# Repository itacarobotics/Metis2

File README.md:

# Metis2
Metis2 is the latest enhanced version of Metis. This project is currently under development, however below is an overview of the changes.

## Mechanics
The new delta robot provides a modular design, with less components and assembly time. An extra degree of freedom has been added to the end effector to rotate around the z-axis. Furthermore, the size of the new robot is significantly smaller than the previous one, therefore it can better fits in smaller environments, such as a small production line.

## Electronics
The control unit of the robot is the BIGTREETECH-SKR-mini-E3 board, which is a main board for 3D printers. Beyond that, a custom PCB has been designed as a shield for the main board, in order to better manage GPIOs and power supply for encoders and motors using terminal blocks.

## Firmware
The control software of the robot is subdivided in two parts based on abstraction levels. The low-level firmware runs on an STM32-G01B1RCT6 micro-controller integrated onto the motherboard. The firmware runs different state machines, each responisble for the comunication, processing data for the trajectory generation and inverse geometry and controlling the closed loop stepper motors. The higher level software controls the position of the robot using the GCODE format.

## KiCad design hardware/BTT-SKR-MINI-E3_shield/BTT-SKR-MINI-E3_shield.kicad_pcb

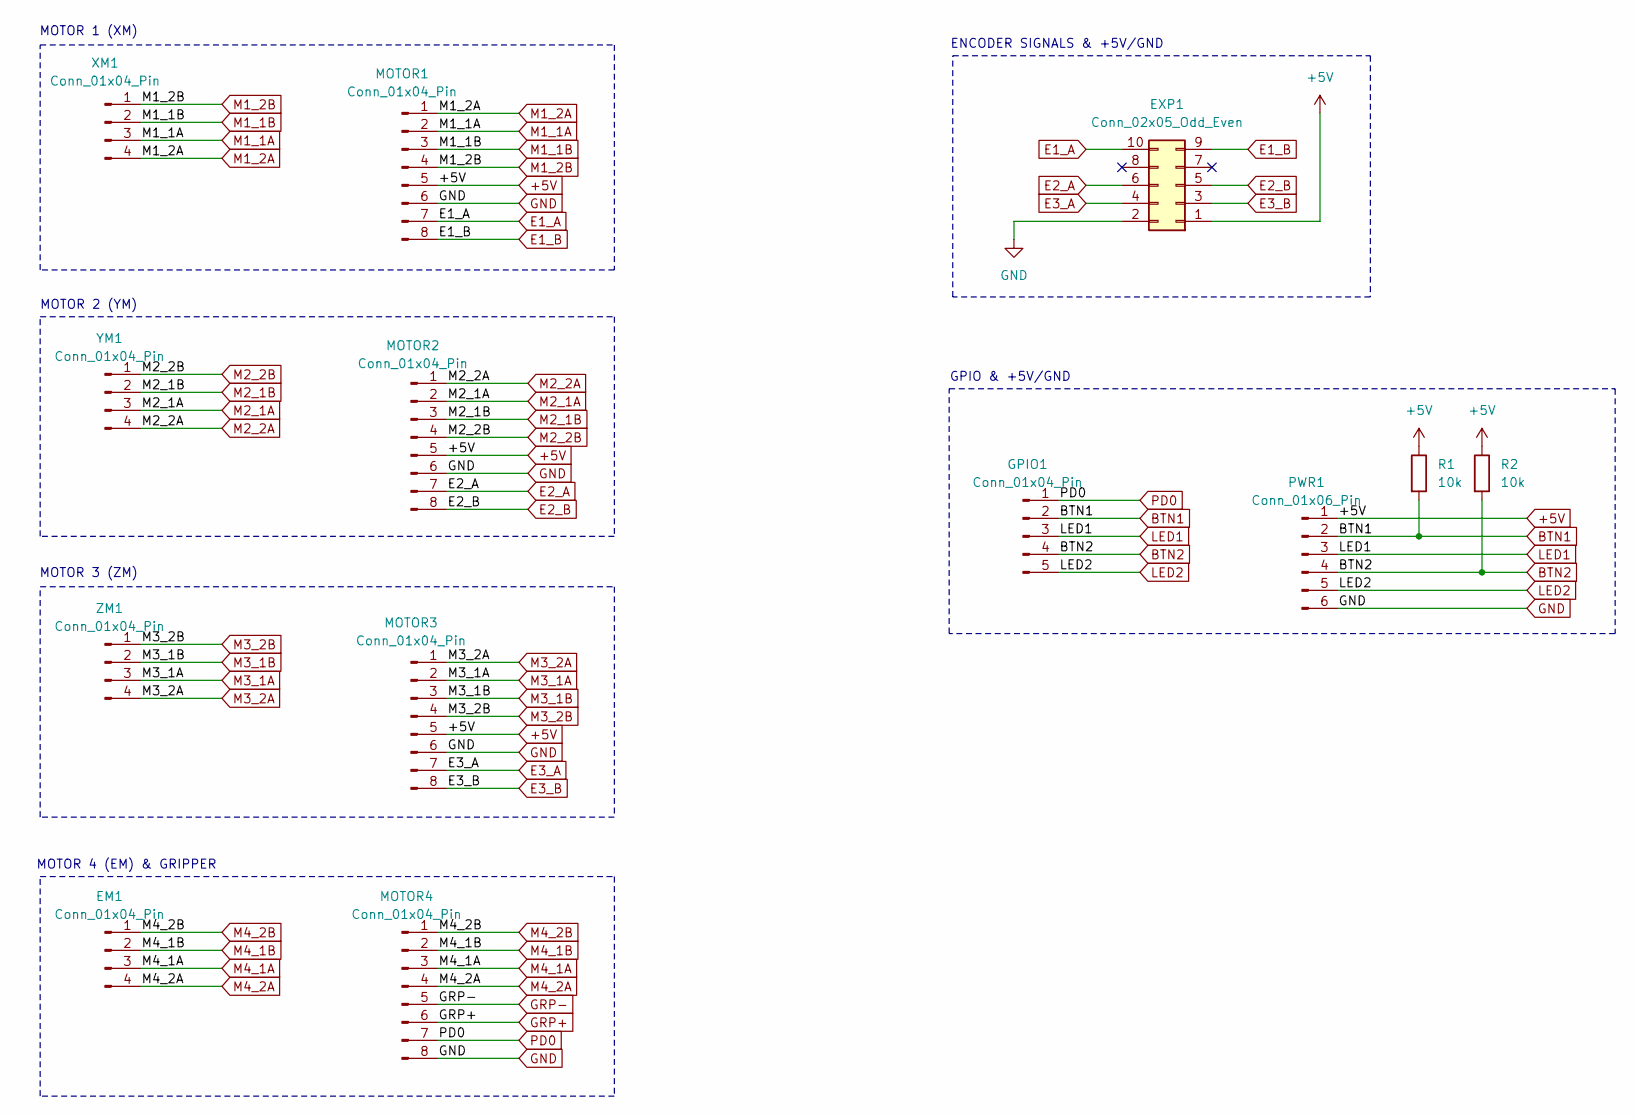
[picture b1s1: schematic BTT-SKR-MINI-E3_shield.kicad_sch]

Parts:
EM1: Conn_01x04_Pin; JST_XH_B4B-XH-A_1x04_P2.50mm_Vertical
EXP1: Conn_02x05_Odd_Even; IDC-Header_2x05_P2.54mm_Vertical
GPIO1: Conn_01x04_Pin; PinHeader_1x05_P2.54mm_Vertical
MOTOR1, MOTOR2, MOTOR3, MOTOR4: Conn_01x04_Pin; MC1.5_8-G-3.5
PWR1: Conn_01x06_Pin; MV1.5_6-G-3.5
R1, R2: 10k; R_0805_2012Metric
XM1: Conn_01x04_Pin; JST_XH_B4B-XH-A_1x04_P2.50mm_Vertical
YM1: Conn_01x04_Pin; JST_XH_B4B-XH-A_1x04_P2.50mm_Vertical
ZM1: Conn_01x04_Pin; JST_XH_B4B-XH-A_1x04_P2.50mm_Vertical

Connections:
+5V: EXP1.1, MOTOR1.5, MOTOR2.5, MOTOR3.5, PWR1.1, R1.1, R2.1
BTN1: GPIO1.2, PWR1.2, R1.2
BTN2: GPIO1.4, PWR1.4, R2.2
E1_A: EXP1.10, MOTOR1.7
E1_B: EXP1.9, MOTOR1.8
E2_A: EXP1.6, MOTOR2.7
E2_B: EXP1.5, MOTOR2.8
E3_A: EXP1.4, MOTOR3.7
E3_B: EXP1.3, MOTOR3.8
GND: EXP1.2, MOTOR1.6, MOTOR2.6, MOTOR3.6, MOTOR4.8, PWR1.6
GRP+: MOTOR4.6; also elsewhere on the board
GRP-: MOTOR4.5; also elsewhere on the board
LED1: GPIO1.3, PWR1.3
LED2: GPIO1.5, PWR1.5
M1_1A: MOTOR1.2, XM1.3
M1_1B: MOTOR1.3, XM1.2
M1_2A: MOTOR1.1, XM1.4
M1_2B: MOTOR1.4, XM1.1
M2_1A: MOTOR2.2, YM1.3
M2_1B: MOTOR2.3, YM1.2
M2_2A: MOTOR2.1, YM1.4
M2_2B: MOTOR2.4, YM1.1
M3_1A: MOTOR3.2, ZM1.3
M3_1B: MOTOR3.3, ZM1.2
M3_2A: MOTOR3.1, ZM1.4
M3_2B: MOTOR3.4, ZM1.1
M4_1A: EM1.3, MOTOR4.3
M4_1B: EM1.2, MOTOR4.2
M4_2A: EM1.4, MOTOR4.4
M4_2B: EM1.1, MOTOR4.1
PD0: GPIO1.1, MOTOR4.7

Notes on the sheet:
ENCODER SIGNALS & +5V/GND
MOTOR 3 (ZM)
MOTOR 4 (EM) & GRIPPER
MOTOR 1 (XM)
GPIO & +5V/GND
MOTOR 2 (YM)

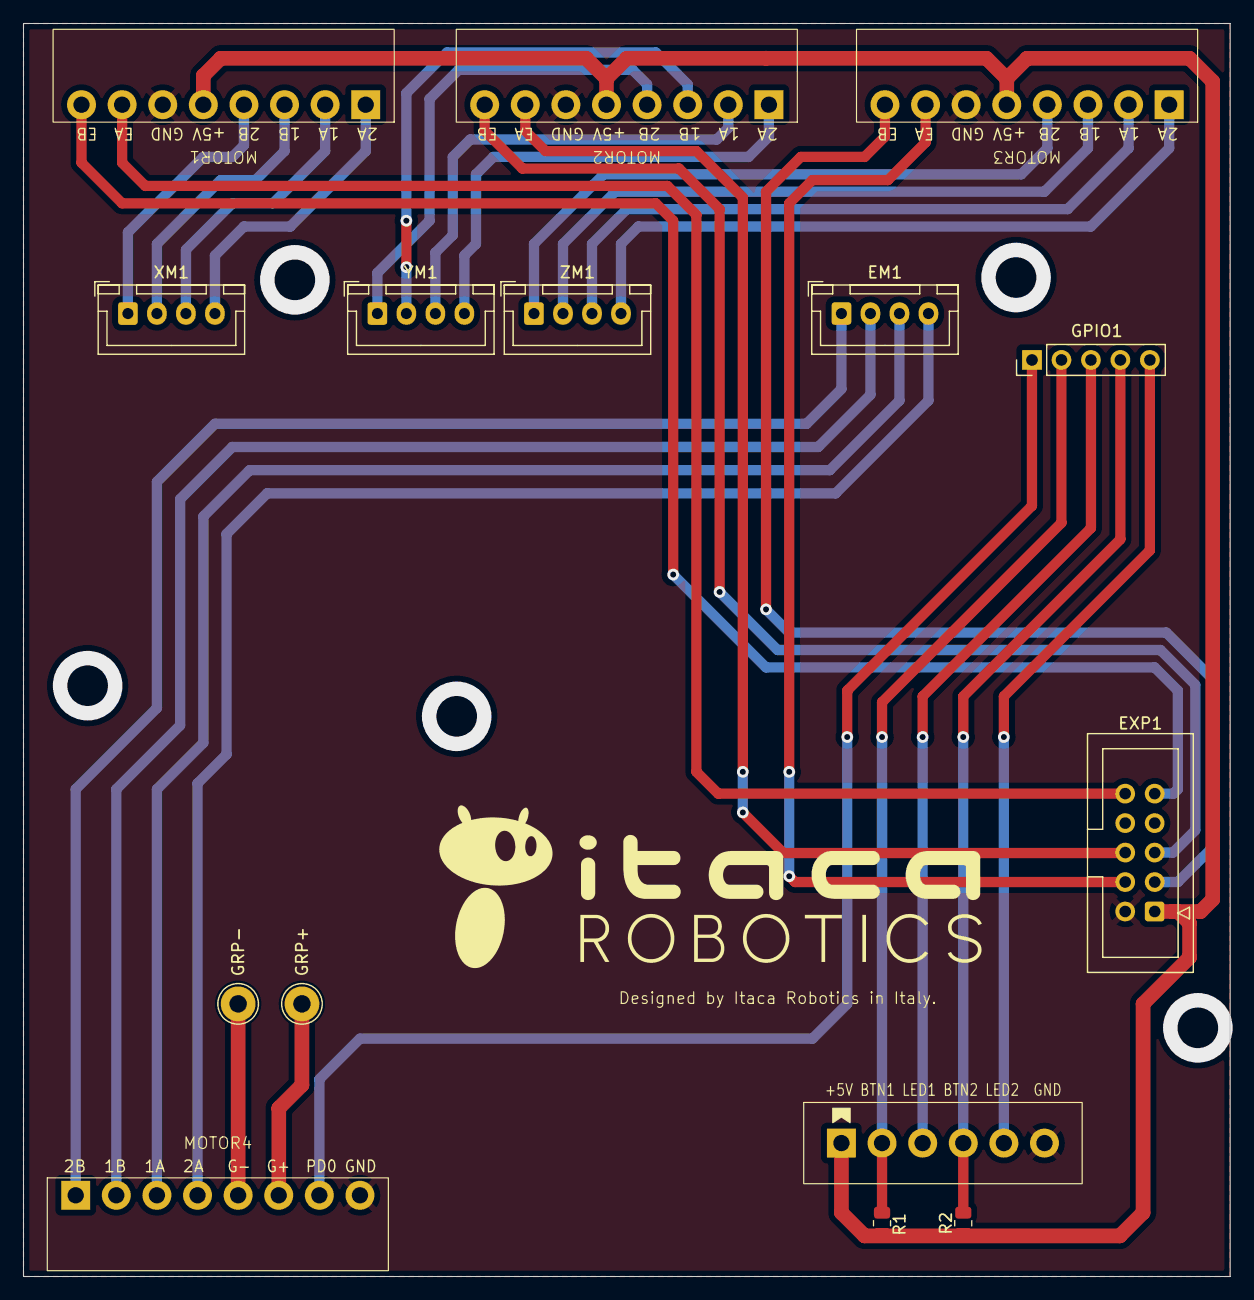
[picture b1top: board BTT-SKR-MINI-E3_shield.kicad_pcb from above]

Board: 2 copper layers, 104.0 x 108.0 mm, 15 parts (0 on the bottom side), 31 nets.

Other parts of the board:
GRP+: TestPoint_THTPad_D3.0mm_Drill1.5mm
GRP-: TestPoint_THTPad_D3.0mm_Drill1.5mm

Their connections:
GRP+: GRP+.1; also elsewhere on the board
GRP-: GRP-.1; also elsewhere on the board

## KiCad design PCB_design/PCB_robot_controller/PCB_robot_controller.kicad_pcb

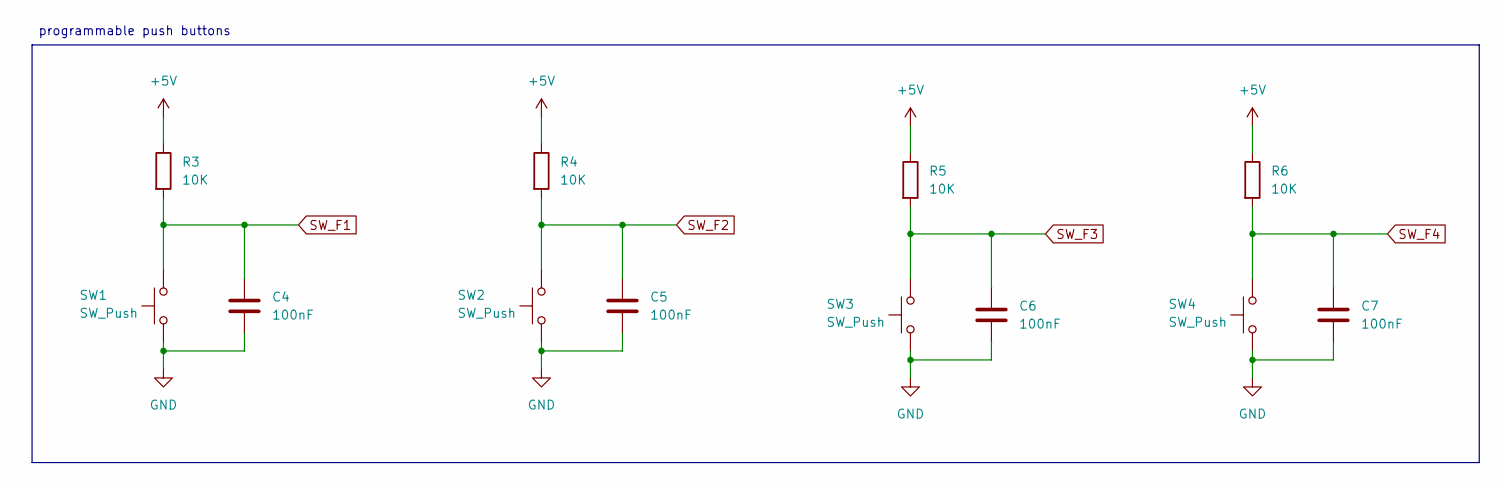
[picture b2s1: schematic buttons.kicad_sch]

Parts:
C4, C5, C6, C7: 100nF; C_0805_2012Metric
R3, R4, R5, R6: 10K; R_0805_2012Metric
SW1, SW2, SW3, SW4: SW_Push; SW_PUSH_6mm_H5mm

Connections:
GND: C4.2, C5.2, C6.2, C7.2, SW1.1, SW2.1, SW3.1, SW4.1; also elsewhere on the board
SW_F1: C4.1, R3.2, SW1.2; also elsewhere on the board
SW_F2: C5.1, R4.2, SW2.2; also elsewhere on the board
SW_F3: C6.1, R5.2, SW3.2; also elsewhere on the board
SW_F4: C7.1, R6.2, SW4.2; also elsewhere on the board

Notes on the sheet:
programmable push buttons

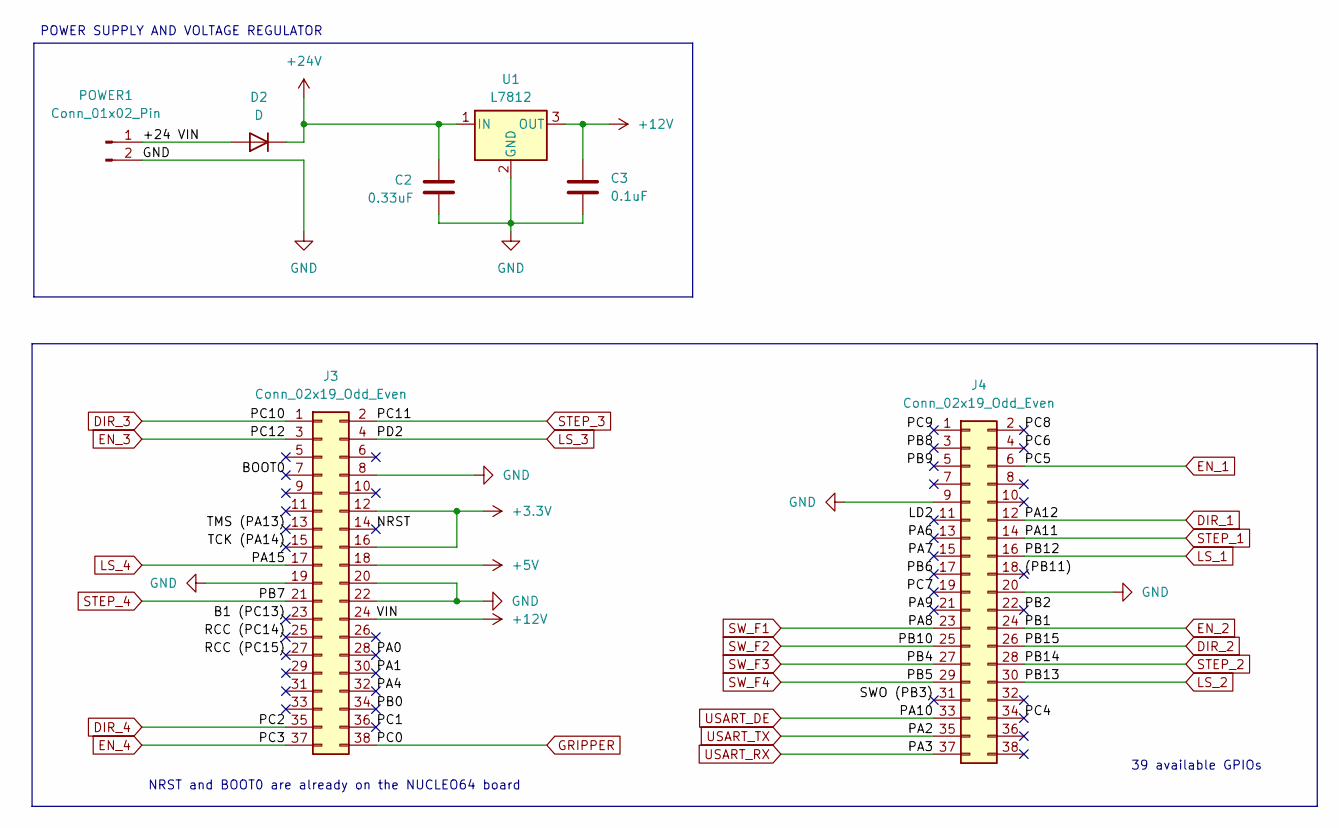
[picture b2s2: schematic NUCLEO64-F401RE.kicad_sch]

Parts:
C2: 0.33uF; C_0805_2012Metric
C3: 0.1uF; C_0805_2012Metric
D2: D; D_0805_2012Metric
J3, J4: Conn_02x19_Odd_Even; PinSocket_2x19_P2.54mm_Vertical
POWER1: Conn_01x02_Pin; TerminalBlock 45 degrees, pitch 3.5mm, 2 pins, WAGO 250-102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
U1: L7812; TO-220-3_Horizontal_TabDown

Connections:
+3.3V: J3.12, J3.16
+12V: C3.1, J3.24, U1.3 (OUT)
+24V: C2.1, D2.1 (K), U1.1 (IN); also elsewhere on the board
/NUCLEO64-F401RE/(PB11): J4.18
/NUCLEO64-F401RE/+24 VIN: D2.2 (A), POWER1.1; also elsewhere on the board
/NUCLEO64-F401RE/B1 (PC13): J3.23
/NUCLEO64-F401RE/BOOT0: J3.7
/NUCLEO64-F401RE/LD2: J4.11
/NUCLEO64-F401RE/NRST: J3.14
/NUCLEO64-F401RE/PA0: J3.28
/NUCLEO64-F401RE/PA1: J3.30
/NUCLEO64-F401RE/PA4: J3.32
/NUCLEO64-F401RE/PA6: J4.13
/NUCLEO64-F401RE/PA7: J4.15
/NUCLEO64-F401RE/PA9: J4.21
/NUCLEO64-F401RE/PB0: J3.34
/NUCLEO64-F401RE/PB2: J4.22
/NUCLEO64-F401RE/PB6: J4.17
/NUCLEO64-F401RE/PB8: J4.3
/NUCLEO64-F401RE/PB9: J4.5
/NUCLEO64-F401RE/PC1: J3.36
/NUCLEO64-F401RE/PC4: J4.34
/NUCLEO64-F401RE/PC6: J4.4
/NUCLEO64-F401RE/PC7: J4.19
/NUCLEO64-F401RE/PC8: J4.2
/NUCLEO64-F401RE/PC9: J4.1
/NUCLEO64-F401RE/RCC (PC14): J3.25
/NUCLEO64-F401RE/RCC (PC15): J3.27
/NUCLEO64-F401RE/SWO (PB3): J4.31
/NUCLEO64-F401RE/TCK (PA14): J3.15
/NUCLEO64-F401RE/TMS (PA13): J3.13
DIR_1: J4.12; also elsewhere on the board
DIR_2: J4.26; also elsewhere on the board
DIR_3: J3.1; also elsewhere on the board
DIR_4: J3.35; also elsewhere on the board
GND: C2.2, C3.2, J3.8, J3.19, J3.20, J3.22, J4.9, J4.20, POWER1.2, U1.2 (GND); also elsewhere on the board
GRIPPER: J3.38; also elsewhere on the board
LS_1: J4.16; also elsewhere on the board
LS_2: J4.30; also elsewhere on the board
LS_3: J3.4; also elsewhere on the board
LS_4: J3.17; also elsewhere on the board
STEP_1: J4.14; also elsewhere on the board
STEP_2: J4.28; also elsewhere on the board
STEP_3: J3.2; also elsewhere on the board
STEP_4: J3.21; also elsewhere on the board
SW_F1: J4.23; also elsewhere on the board
SW_F2: J4.25; also elsewhere on the board
SW_F3: J4.27; also elsewhere on the board
SW_F4: J4.29; also elsewhere on the board
USART_DE: J4.33; also elsewhere on the board
USART_RX: J4.37; also elsewhere on the board
USART_TX: J4.35; also elsewhere on the board

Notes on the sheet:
39 available GPIOs
POWER SUPPLY AND VOLTAGE REGULATOR
NRST and BOOT0 are already on the NUCLEO64 board

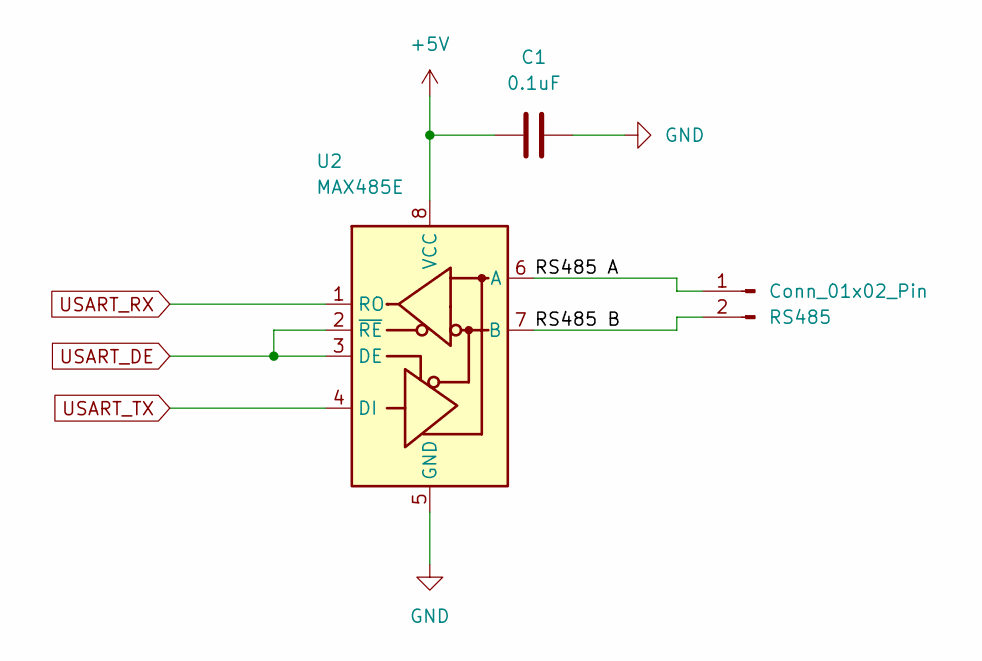
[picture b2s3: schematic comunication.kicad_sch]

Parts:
C1: 0.1uF; C_0805_2012Metric
RS485: Conn_01x02_Pin; TerminalBlock 45 degrees, pitch 3.5mm, 2 pins, WAGO 250-102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
U2: MAX485E; SO-8_3.9x4.9mm_P1.27mm

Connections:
/comunication/RS485 A: RS485.1, U2.6 (A); also elsewhere on the board
/comunication/RS485 B: RS485.2, U2.7 (B); also elsewhere on the board
GND: C1.2, U2.5 (GND); also elsewhere on the board
USART_DE: U2.2 (~RE), U2.3 (DE); also elsewhere on the board
USART_RX: U2.1 (RO); also elsewhere on the board
USART_TX: U2.4 (DI); also elsewhere on the board

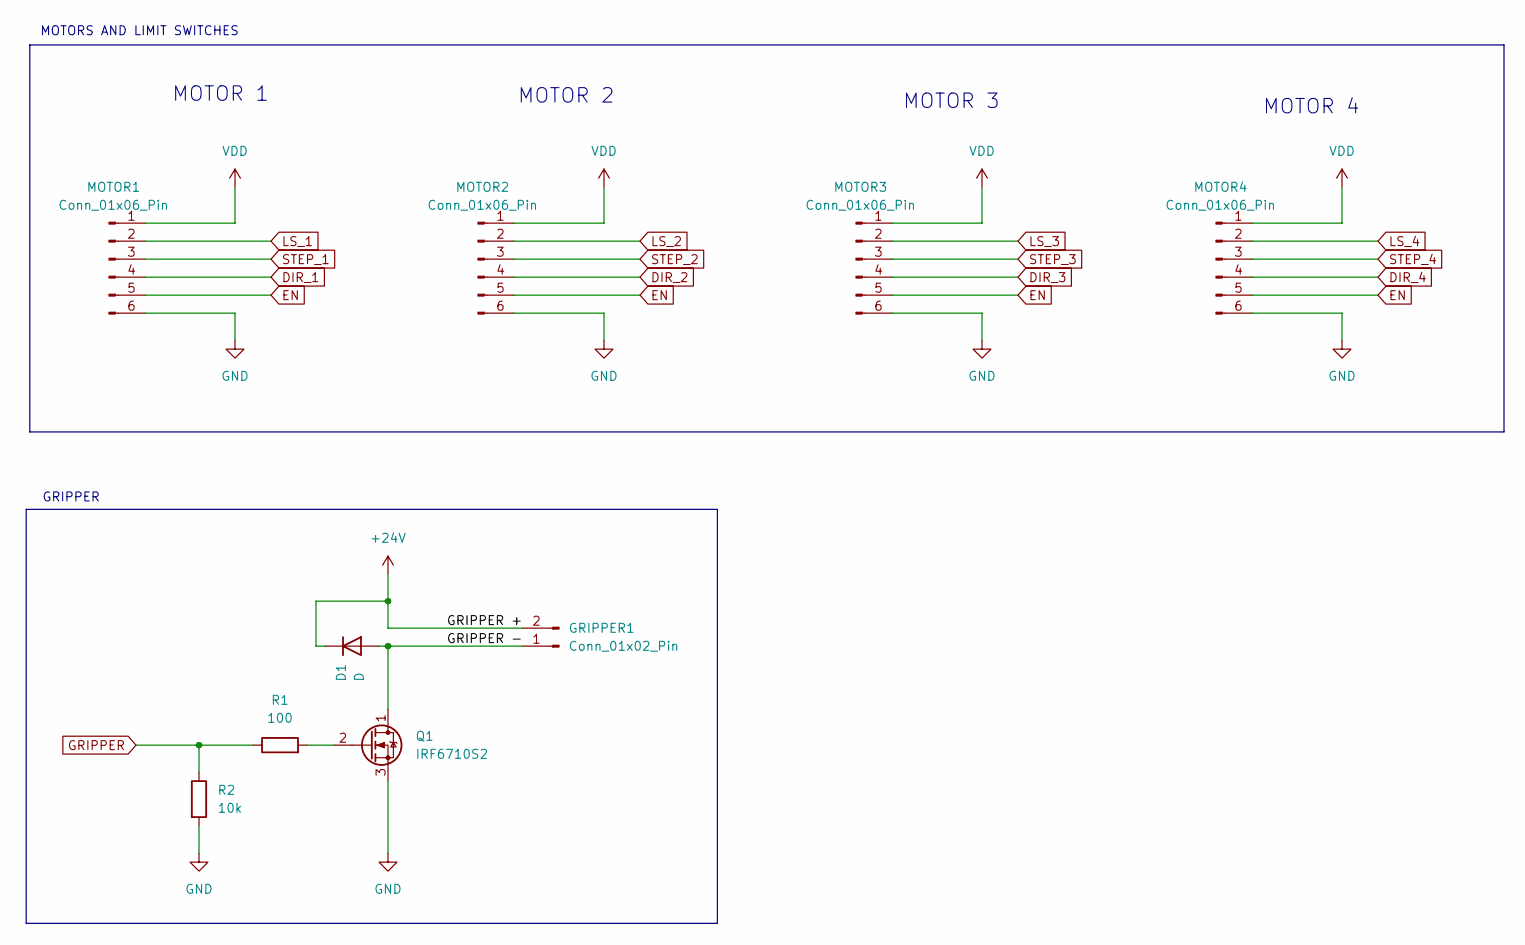
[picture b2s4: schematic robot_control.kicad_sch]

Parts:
D1: D; D_0805_2012Metric
GRIPPER1: Conn_01x02_Pin; TerminalBlock 45 degrees, pitch 3.5mm, 2 pins, WAGO 250-102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
MOTOR1, MOTOR2, MOTOR3, MOTOR4: Conn_01x06_Pin; TerminalBlock 45 degrees, pitch 3.5mm, 6 pins, WAGO 250-102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
Q1: IRF6710S2; TO-220-3_Vertical
R1: 100; R_0805_2012Metric
R2: 10k; R_0805_2012Metric

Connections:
+24V: D1.1 (K), GRIPPER1.2; also elsewhere on the board
/robot_control/GRIPPER -: D1.2 (A), GRIPPER1.1, Q1.1 (D); also elsewhere on the board
DIR_1: MOTOR1.4; also elsewhere on the board
DIR_2: MOTOR2.4; also elsewhere on the board
DIR_3: MOTOR3.4; also elsewhere on the board
DIR_4: MOTOR4.4; also elsewhere on the board
GND: MOTOR1.6, MOTOR2.6, MOTOR3.6, MOTOR4.6, Q1.3 (S), R2.2; also elsewhere on the board
GRIPPER: R1.1, R2.1; also elsewhere on the board
LS_1: MOTOR1.2; also elsewhere on the board
LS_2: MOTOR2.2; also elsewhere on the board
LS_3: MOTOR3.2; also elsewhere on the board
LS_4: MOTOR4.2; also elsewhere on the board
unnamed: Q1.2 (G), R1.2
STEP_1: MOTOR1.3; also elsewhere on the board
STEP_2: MOTOR2.3; also elsewhere on the board
STEP_3: MOTOR3.3; also elsewhere on the board
STEP_4: MOTOR4.3; also elsewhere on the board

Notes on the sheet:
MOTOR 2
MOTOR 4
MOTORS AND LIMIT SWITCHES
MOTOR 3
GRIPPER
MOTOR 1

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
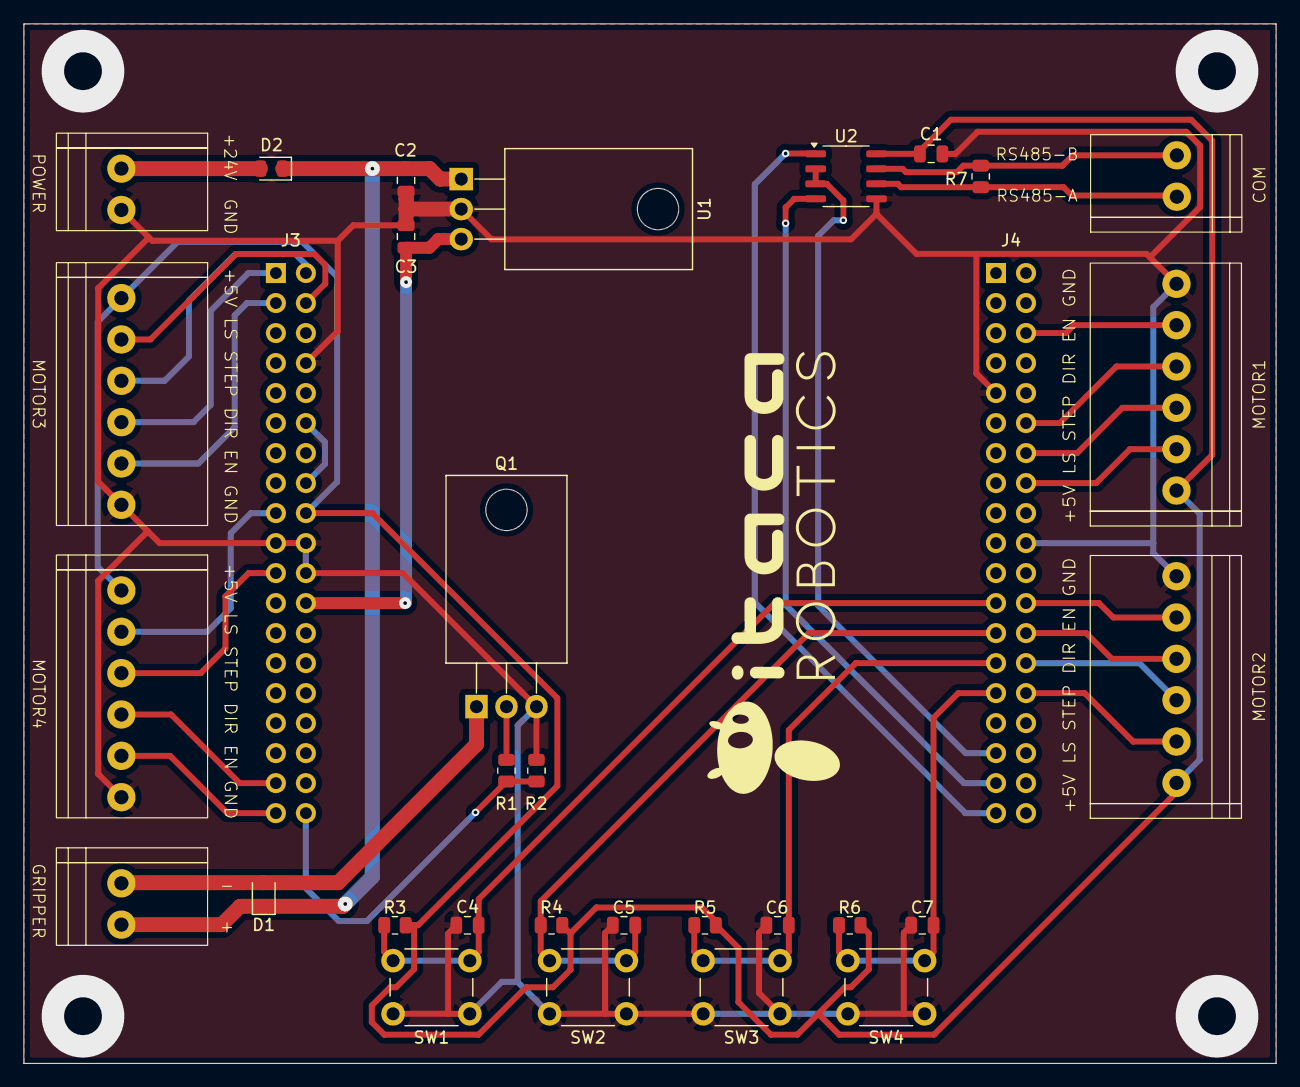
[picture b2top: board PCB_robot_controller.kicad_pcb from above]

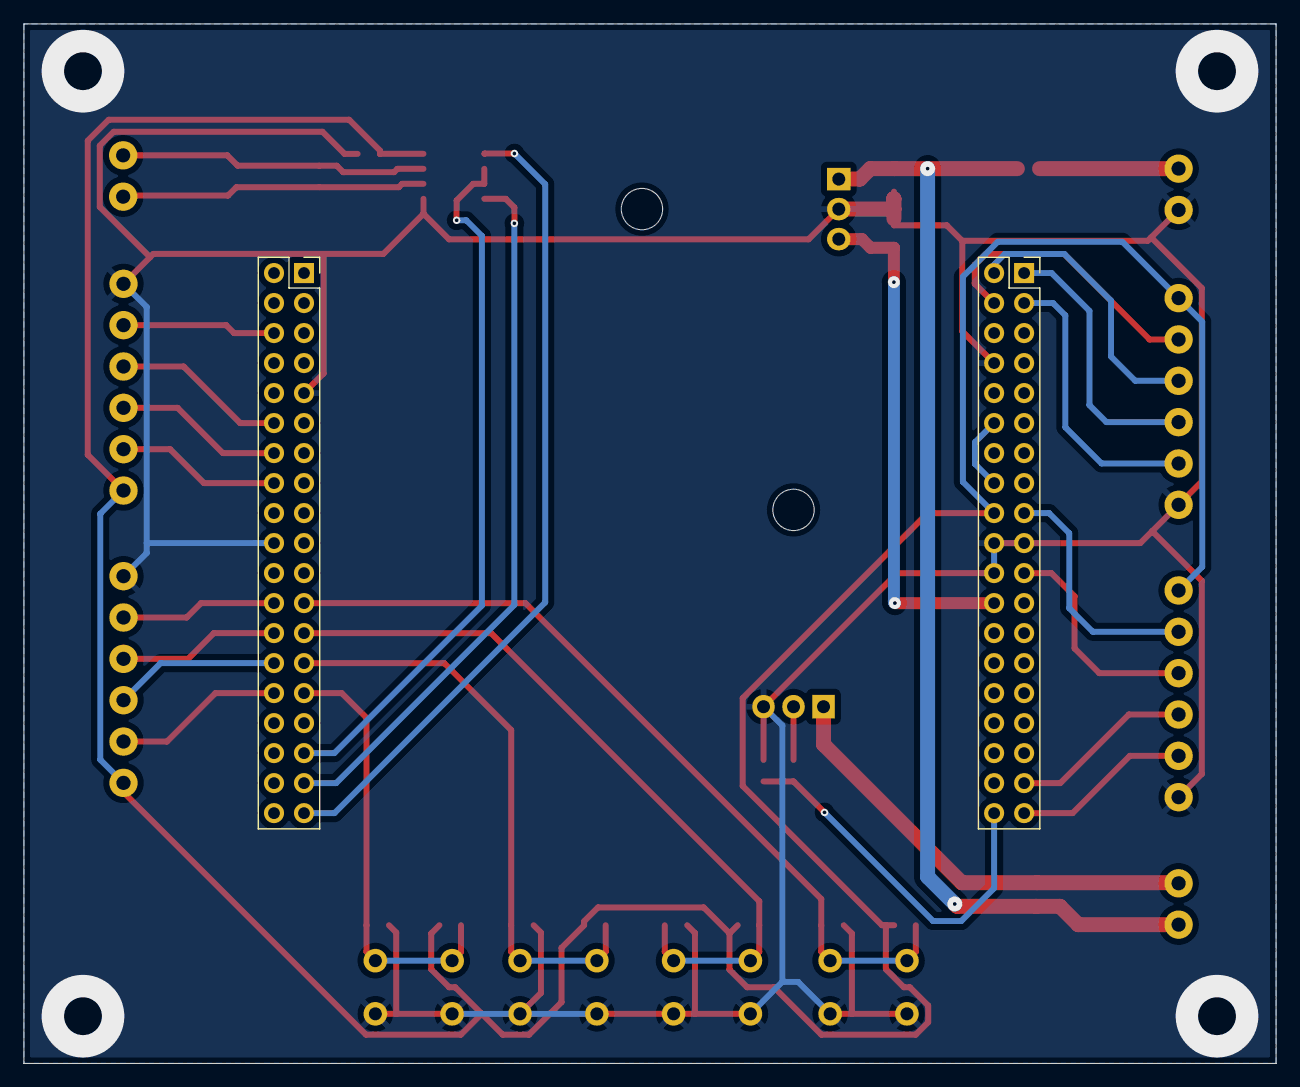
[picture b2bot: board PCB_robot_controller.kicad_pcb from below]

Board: 2 copper layers, 106.0 x 88.0 mm, 32 parts (2 on the bottom side), 34 nets.

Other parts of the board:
COM: Conn_01x02_Pin; TerminalBlock 45 degrees, pitch 3.5mm, 2 pins, WAGO 250-102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
GRIPPER: Conn_01x02_Pin; TerminalBlock 45 degrees, pitch 3.5mm, 2 pins, WAGO 250-102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
POWER: Conn_01x02_Pin; TerminalBlock 45 degrees, pitch 3.5mm, 2 pins, WAGO 250-102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
R7: 120; R_0805_2012Metric

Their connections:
+24V: GRIPPER.2; also elsewhere on the board
/NUCLEO64-F401RE/+24 VIN: POWER.1; also elsewhere on the board
/comunication/RS485 A: COM.1, R7.1; also elsewhere on the board
/comunication/RS485 B: COM.2, R7.2; also elsewhere on the board
/robot_control/GRIPPER -: GRIPPER.1; also elsewhere on the board
GND: POWER.2; also elsewhere on the board

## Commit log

2024-08-16 init
2024-08-24 pcb to production
2024-09-04 added modules
2024-09-06 added ig
2024-09-06 ig is correct
2024-09-07 added trj template
2024-09-09 trajectory planning works
2024-09-09 added comments
2024-09-10 trajectory generator optimized
2024-09-10 update dr
2024-09-11 a lot of changes
2024-09-12 added motion planning fsm
2024-09-13 cmake, motion planner, buffer
2024-09-22 added fsm middleware
2024-09-24 added init
2024-09-28 changed folder path
2024-10-23 readme
